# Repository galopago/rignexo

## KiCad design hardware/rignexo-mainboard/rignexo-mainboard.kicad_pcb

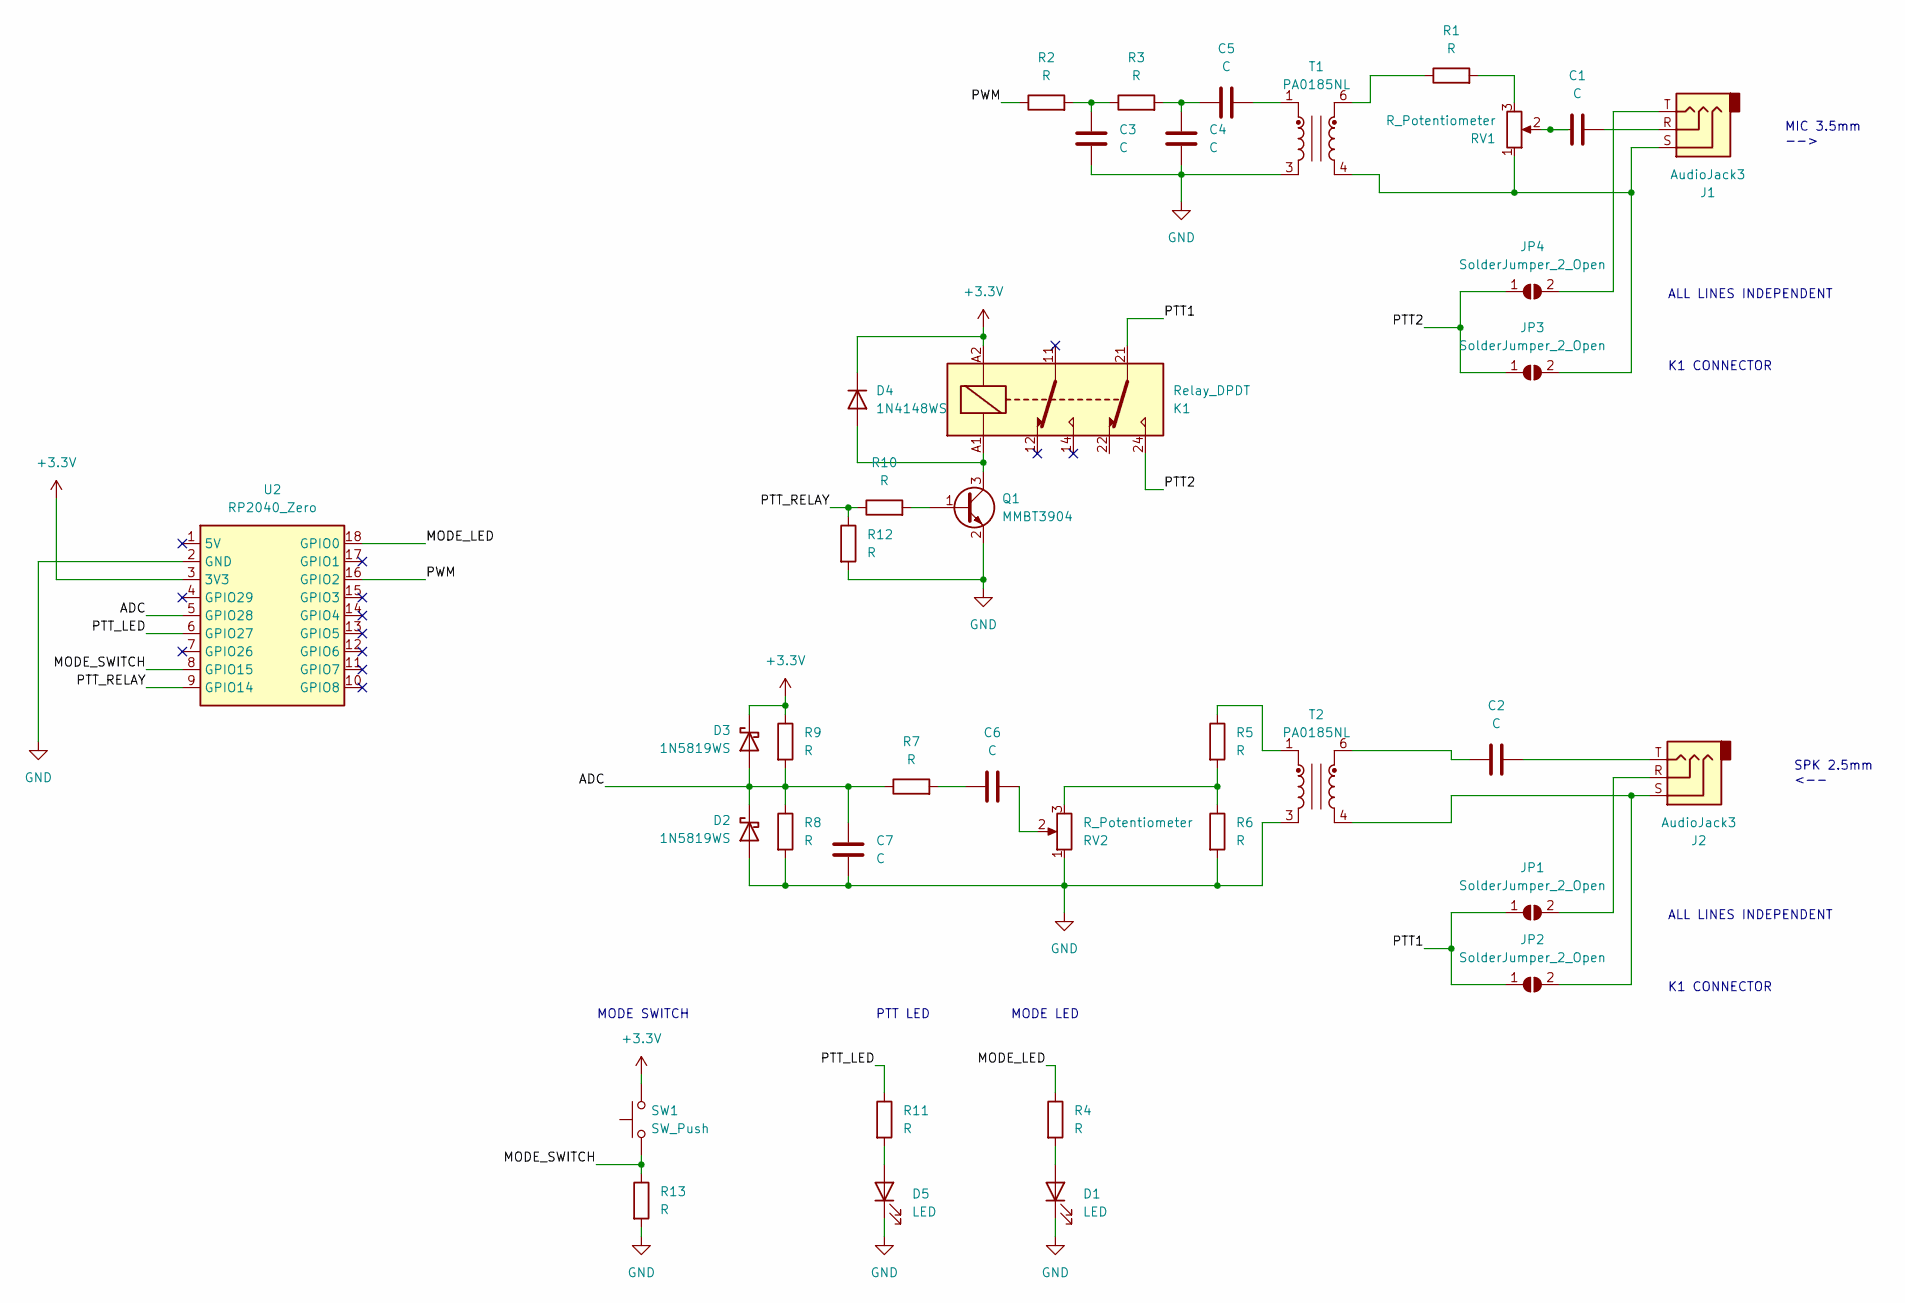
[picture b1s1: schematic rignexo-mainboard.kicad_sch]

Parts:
C1, C2, C3, C4, C5, C6, C7: C; C_0805_2012Metric_Pad1.18x1.45mm_HandSolder
D1, D5: LED; LED_0805_2012Metric_Pad1.15x1.40mm_HandSolder
D2, D3: 1N5819WS; D_SOD-323_HandSoldering
D4: 1N4148WS; D_SOD-323_HandSoldering
J1: AudioJack3; Jack_3.5mm_PJ-3200_Horizontal
J2: AudioJack3; Jack_2.5mm_PJ-211A-12H_Horizontal
JP1, JP2, JP3, JP4: SolderJumper_2_Open; SolderJumper-2_P1.3mm_Open_RoundedPad1.0x1.5mm
K1: Relay_DPDT; Relay_DPDT_Omron_G6K-2F-Y
Q1: MMBT3904; SOT-23
R1, R2, R3, R4, R5, R6, R7, R8, R9, R10, R11, R12, R13: R; R_0805_2012Metric_Pad1.20x1.40mm_HandSolder
RV1, RV2: R_Potentiometer; Potentiometer_Bourns_3006P_Horizontal
SW1: SW_Push; SW_SMD_Push_3X4mm_2_pin
T1, T2: PA0185NL; Transformer_ED8-SMD_10.5x8.0mm_P5.00-LS14.0_4Pin
U2: RP2040_Zero; RP2040 Zero

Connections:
+3.3V: D3.1 (K), D4.1 (K), K1.A2, R9.1, SW1.2, U2.3 (3V3)
/ADC: C7.1, D2.1 (K), D3.2 (A), R7.1, R8.1, R9.2, U2.5 (GPIO28)
/MODE_LED: R4.1, U2.18 (GPIO0)
/MODE_SWITCH: R13.1, SW1.1, U2.8 (GPIO15)
/PTT1: JP1.1 (A), JP2.1 (A), K1.21
/PTT2: JP3.1 (A), JP4.1 (A), K1.24
/PTT_LED: R11.1, U2.6 (GPIO27)
/PTT_RELAY: R10.1, R12.1, U2.9 (GPIO14)
/PWM: R2.1, U2.16 (GPIO2)
GND: C3.1, C4.2, C7.2, D1.1 (K), D2.2 (A), D5.1 (K), Q1.2 (E), R6.2, R8.2, R12.2, R13.2, RV2.1, T1.3, T2.3, U2.2 (GND)
unnamed: C1.1, RV1.2
unnamed: C1.2, J1.R
unnamed: C2.1, T2.6
unnamed: C2.2, J2.T
unnamed: C3.2, R2.2, R3.1
unnamed: C4.1, C5.1, R3.2
unnamed: C5.2, T1.1
unnamed: C6.1, R7.2
unnamed: C6.2, RV2.2
unnamed: D1.2 (A), R4.2
unnamed: D4.2 (A), K1.A1, Q1.3 (C)
unnamed: D5.2 (A), R11.2
unnamed: J2.R, JP1.2 (B)
unnamed: J2.S, JP2.2 (B), T2.4
unnamed: J1.S, JP3.2 (B), RV1.1, T1.4
unnamed: J1.T, JP4.2 (B)
unnamed: Q1.1 (B), R10.2
unnamed: R1.1, T1.6
unnamed: R1.2, RV1.3
unnamed: R5.1, T2.1
unnamed: R5.2, R6.1, RV2.3

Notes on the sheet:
ALL LINES INDEPENDENT
MODE SWITCH
SPK 2.5mm <--
MIC 3.5mm -->
PTT LED
K1 CONNECTOR
MODE LED

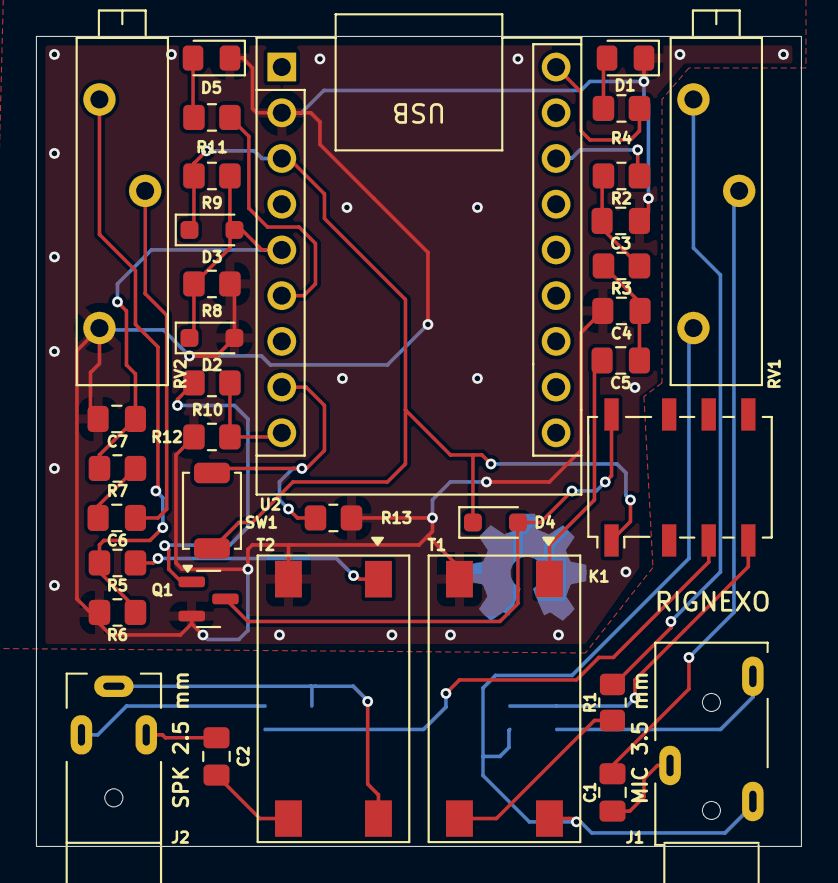
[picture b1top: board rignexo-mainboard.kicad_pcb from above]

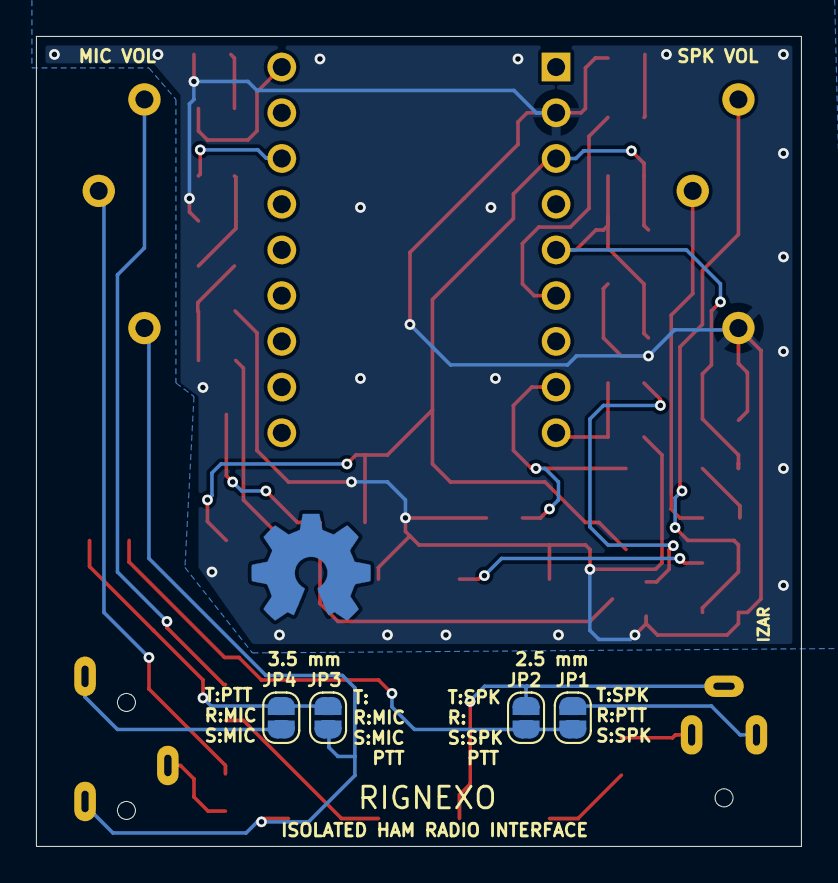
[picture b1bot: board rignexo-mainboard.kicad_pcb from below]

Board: 2 copper layers, 42.5 x 45.0 mm, 39 parts (4 on the bottom side), 31 nets.
